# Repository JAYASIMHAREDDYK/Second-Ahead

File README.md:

# SECONDS AHEAD (A-ADAS)

<div align="center">

### Automotive Pre-Crash Early Warning, Dual-Sector Acoustic Radar & Kinematic Telemetry Cockpit

<!-- Primary System Badges -->
[-E63946?style=flat-square&logo=espressif&logoColor=white)](https://www.espressif.com/)
[-00B4D8?style=flat-square&logo=googlechrome&logoColor=white)](https://developer.mozilla.org/en-US/docs/Web/API/Web_Serial_API)

<br/>

<!-- Horizontal Mini Tech Stack Icons -->

<br/>

<!-- Performance Badges -->

</div>

<br/>

```
     [Front HC-SR04: Sensor A] ──┐
                                 ├──► [ESP32-H2 RISC-V SoC] ──► USB CDC UART (115200 8N1) ──► [Web Dashboard]
     [Side HC-SR04: Sensor B]  ──┤          ▲                                                        │
                                 │          │ 12ms Non-Blocking Acoustic Interleaving                ├─► Telemetry Cluster
     [TCRT5000 IR Contact: U4] ──┘          ▼                                                        ├─► 2D Kinematic Simulator
                                      [16x2 I2C LCD]                                                 └─► Trilingual Voice AI
```

---

## Table of Contents

- [Overview](#overview)
- [System Architecture](#system-architecture)
- [Key Technical Specifications](#key-technical-specifications)
- [Hardware Bench Wiring and Pinout Schedule](#hardware-bench-wiring-and-pinout-schedule)
- [Kinematics and Threat Assessment Engine](#kinematics-and-threat-assessment-engine)
- [High-Speed Telemetry Protocol](#high-speed-telemetry-protocol)
- [Telemetry Dashboard and 2D Incident Simulator](#telemetry-dashboard-and-2d-incident-simulator)
- [Trilingual Cockpit Voice AI](#trilingual-cockpit-voice-ai)
- [Ground-Truth Physical Impact Audit](#ground-truth-physical-impact-audit)
- [Getting Started](#getting-started)
- [Technical Dossier and Engineering Deliverables](#technical-dossier-and-engineering-deliverables)
- [Project Structure](#project-structure)
- [License](#license)

---

## Overview

**SECONDS AHEAD** is an automotive pre-crash detection and active cockpit alert system engineered on the **ESP32-H2 RISC-V microcontroller**. It bridges low-level real-time acoustic sensing with an instrument-grade web telemetry cluster and neural voice synthesis to deliver verifiable collision lead time.

Standard ultrasonic parking systems suffer from severe cross-echo interference, high cycle latency, and tunnel-vision frontal coverage that leaves intersection blind spots vulnerable. SECONDS AHEAD resolves these challenges through:

1. **Dual-Sector Acoustic Radar**: Frontal longitudinal tracking (**Sensor A**, 2–100 cm) paired with an orthogonal 90° lateral sensor (**Sensor B** for intersection cross-traffic), paced with 12ms non-blocking ping interleaving to prevent ultrasonic packet collisions.
2. **Deterministic Ground-Truth Lead-Time Audit**: An integrated **TCRT5000 infrared reflective sensor (U4)** positioned at the bumper barrier records the exact microsecond timestamp of physical impact. The system automatically computes and audits the advance warning margin ($\Delta t_{\text{lead}} = t_{\text{contact}} - t_{\text{warning}}$).
3. **Web Serial Telemetry Dashboard**: A zero-dependency single-file frontend running directly in Chromium-based browsers, visualizing live 20 Hz telemetry with rolling strip charts, dynamic proximity bars, and threat transition timelines.
4. **2D Kinematic Incident Simulator**: A real-time physics replayer simulating road kinematics, dual radar beam cones, lateral vehicle intrusions, safety boundaries, and collision shockwave dynamics.
5. **Trilingual Cockpit Voice AI**: Calm, authoritative ADAS audio warnings in **English**, **हिंदी (Hindi)**, and **ಕನ್ನಡ (Kannada)** powered by **ElevenLabs Creator Plan (Turbo v2.5)** with an in-memory audio object cache for **0 ms repeat latency**.

---

## System Architecture

```mermaid
graph TD
    subgraph Hardware ["Hardware Subsystem (ESP32-H2 Dev Module)"]
        SA["Sensor A: Front HC-SR04 (GPIO 10 / 11)"] -->|Longitudinal Ping| MCU["ESP32-H2 RISC-V SoC"]
        SB["Sensor B: Lateral HC-SR04 (GPIO 14 / 01)"] -->|12ms Interleaved Ping| MCU
        IR["Sensor U4: TCRT5000 IR (GPIO 12)"] -->|Bumper Impact Trigger| MCU
        BTN["Mute Switch (GPIO 24)"] -->|Mute Toggle| MCU

        MCU -->|I2C Fast Mode 400kHz| LCD["16x2 Character LCD (0x27)"]
        MCU -->|Parallel Digital Drive| LED_R["Red Strobe LEDs (High Risk)"]
        MCU -->|Digital Output| LED_B["Blue Monitor LED"]
        MCU -->|Tone Frequency Output| BZ["Acoustic Piezo Buzzer"]
    end

    subgraph Telemetry ["Serial Data Stream"]
        MCU -->|USB CDC UART 115200 8N1| WS["Web Serial Interface"]
    end

    subgraph Frontend ["Dashboard and Incident Simulator (index.html)"]
        WS --> PARSER["CSV Packet Parser"]
        PARSER --> CLUSTER["Telemetry Cluster (Gauges, Strip Chart, Timeline)"]
        PARSER --> SIM["2D Kinematic Simulator (Radar Cones, Car Physics)"]
        PARSER --> AUDIT["Ground-Truth Audit (Lead Time and Median Stats)"]
        PARSER --> VOICE["Neural Voice Engine (ElevenLabs Turbo / Web Speech)"]

        VOICE -->|Audio Playback| SPK["Trilingual Cockpit Audio"]
        SIM -->|MediaRecorder| VID["WebM Video Clip Exporter"]
        CLUSTER -->|Data Export| CSV["CSV Telemetry Downloader"]
    end
```

---

## Key Technical Specifications

| Parameter | Specification | Functional Details |
| :--- | :--- | :--- |
| **Microcontroller Unit** | ESP32-H2-DevKitM-1 | 32-bit RISC-V Single-Core @ 96 MHz, Native USB CDC |
| **Operating Voltage** | 3.3V DC Logic | Onboard LDO regulator with low-impedance common ground plane |
| **Longitudinal Sensor (A)** | HC-SR04 Ultrasonic | 2 cm to 100 cm active detection range, forward cone |
| **Lateral Sensor (B)** | HC-SR04 Ultrasonic | 90° blind-spot cross-traffic monitoring |
| **Interleaving Interval** | 12 ms non-blocking delay | Eliminates cross-reflection acoustic interference between sensors |
| **Ground-Truth Detector** | TCRT5000 Optical IR | Active-low bumper impact trigger for microsecond timestamping |
| **Telemetry Interface** | USB CDC Serial (115200 baud, 8N1) | Fixed-format ASCII CSV packets streamed at 18–20 Hz |
| **Cockpit Display** | 16x2 Character LCD | PCF8574 I2C backpack @ `0x27`, 400 kHz with 30ms timeout |
| **Visual Alert Indicators** | High-Intensity 5mm LEDs | Dual Red strobes (GPIO 0, 13) + Blue monitor LED (GPIO 4) |
| **Acoustic Sounder** | 3.3V Piezo Transducer | Pulsed frequency audio alert on GPIO 5 |
| **Dashboard Architecture** | Vanilla HTML5 / CSS3 / ES6 | Single zero-dependency file (`index.html`) using Web Serial API |
| **Voice AI Synthesis** | ElevenLabs `eleven_turbo_v2_5` | Sub-300ms neural streaming synthesis with 0ms memory cache |
| **Cockpit Alert Languages** | Trilingual (EN, HI, KN) | Authoritative, non-ragebaiting ADAS driving alerts |

---

## Hardware Bench Wiring and Pinout Schedule

<div align="center">
  
  <p><em>Figure 1: SECONDS AHEAD Hardware Prototype with numbered subsystem callouts.</em></p>
</div>

### Pinout Connection Schedule

| Pin Identifier | Signal Name | Connected Peripheral | Logic Level | Direction | Operational Role |
| :---: | :---: | :---: | :---: | :---: | :--- |
| **GPIO 10** | `TRIG_A` | Front HC-SR04 (Pin 2) | 3.3V | Output | 10 µs ultrasonic burst trigger |
| **GPIO 11** | `ECHO_A` | Front HC-SR04 (Pin 3) | 3.3V | Input | Longitudinal flight pulse measurement |
| **GPIO 14** | `TRIG_B` | Lateral HC-SR04 (Pin 2) | 3.3V | Output | 12 ms interleaved lateral burst trigger |
| **GPIO 01** | `ECHO_B` | Lateral HC-SR04 (Pin 3) | 3.3V | Input | Lateral acoustic flight measurement |
| **GPIO 12** | `PIN_IR` | TCRT5000 IR Sensor (OUT) | 3.3V | Input (PU) | Active LOW physical contact detection |
| **GPIO 22** | `I2C_SDA` | LCD PCF8574 Backpack | 3.3V | Bidirectional | I2C Serial Data (400 kHz Fast Mode) |
| **GPIO 23** | `I2C_SCL` | LCD PCF8574 Backpack | 3.3V | Output | I2C Serial Clock (30 ms timeout recovery) |
| **GPIO 00 & 13** | `RED_ALERT` | Red 5mm LEDs (Dual 220Ω) | 3.3V | Output | High-current parallel drive for HIGH_RISK strobe |
| **GPIO 04** | `BLUE_MON` | Blue 5mm LED (220Ω) | 3.3V | Output | Steady illumination for MONITOR threat level |
| **GPIO 05** | `BUZZER` | Piezo Buzzer Transducer | 3.3V | Output | Pulsed audible collision alarm |
| **GPIO 24** | `MUTE_SW` | Tactile Button to GND | 3.3V | Input (PU) | Active-low cockpit buzzer mute toggle |
| **3V3 & GND** | `PWR / GND`| Power Distribution Rails | 3.3V / 0V | Power | Regulated 3.3V power and ground return |

---

## Kinematics and Threat Assessment Engine

The ESP32-H2 firmware continuously calculates relative target kinematics using rolling median filtering and first-derivative linear regression.

### Mathematical Formulation

1. **Longitudinal Distance Measurement**:
   $$d(t) = \frac{\Delta t_{\text{echo}} \times 0.0343}{2} \quad [\text{cm}]$$

2. **Closing Velocity Calculation**:
   $$v(t) = -\frac{d(t) - d(t - \Delta t)}{\Delta t} \quad [\text{cm/s}]$$
   *(A positive velocity value denotes an object actively closing distance towards the vehicle).*

3. **Time-to-Collision (TTC)**:
   $$\text{TTC}(t) = \frac{d(t)}{v(t)} \quad [\text{s}]$$
   *(Computed only when $v(t) \ge 4.0\text{ cm/s}$. Evaluated as invalid ($-1.0\text{ s}$) when the target is static or receding).*

### Finite State Machine (FSM)

```
                            Target Observed (d <= 100 cm)
         ┌──────────────────────────────────────────────────────────────────┐
         │                                                                  │
         ▼                                                                  │
    ┌─────────┐         v < 4 cm/s          ┌──────────────┐                │
    │  WAIT   │ ──────────────────────────► │ NO APPROACH  │                │
    └─────────┘                             └──────────────┘                │
         ▲                                         │                        │
         │ No Target                               │ v >= 4 cm/s            │
         │                                         ▼                        │
         │                                  ┌──────────────┐                │
         │                                  │  UNCERTAIN   │ (Fast path)    │
         │                                  └──────────────┘                │
         │                                         │                        │
         │                                         │ Streak >= 2 & TTC > 3s │
         │                                         ▼                        │
         │                                  ┌──────────────┐                │
         │                                  │   MONITOR    │ (TTC 3.0s–5.0s)│
         │                                  └──────────────┘                │
         │                                         │                        │
         │                                         │ d < 50cm OR TTC <= 3.0s│
         │                                         ▼                        │
         │                                  ┌──────────────┐                │
         └───────────────────────────────── │  HIGH RISK   │ (Strobe/Alarm) │
              Physical Impact / Reset       └──────────────┘                │
                                                   │                        │
                                                   └────────────────────────┘
```

- **WAIT**: Target beyond 100 cm. All visual and audible alarms remain silent.
- **NO APPROACH**: Target detected within 100 cm but stationary or moving away ($v < 4\text{ cm/s}$).
- **UNCERTAIN**: Closing motion detected ($v \ge 4\text{ cm/s}$); establishing trajectory persistence over multiple pings.
- **MONITOR**: Verified approach trajectory with $3.0\text{ s} < \text{TTC} \le 5.0\text{ s}$ and $d > 50\text{ cm}$. Solid Blue LED enabled.
- **HIGH RISK**: Critical condition where $\text{TTC} \le 3.0\text{ s}$ or $d < 50\text{ cm}$. Triggers 3 Hz Red strobe LEDs, pulsed audio tone, and cockpit voice alert.

---

## High-Speed Telemetry Protocol

Telemetry is transmitted over USB CDC serial at **115200 baud, 8N1** in fixed-width comma-separated ASCII records at 18–20 Hz.

### Telemetry Packet Format
```
ms,dist_cm,speed_cms,ttc_s,state,ir,muted,side_cm
14250,38.2,21.4,1.78,HIGH RISK,1,0,68.4
```

| Field Index | Key | Units | Data Type | Definition |
| :---: | :--- | :---: | :---: | :--- |
| `0` | `ms` | milliseconds | integer | System elapsed uptime via `millis()` |
| `1` | `dist_cm` | centimeters | float | Sensor A longitudinal target distance |
| `2` | `speed_cms` | cm / second | float | Target closing speed relative to host |
| `3` | `ttc_s` | seconds | float | Time to collision; `-1.0` if inactive |
| `4` | `state` | — | string | Threat level: `WAIT`, `MONITOR`, `HIGH RISK` |
| `5` | `ir` | 0 or 1 | integer | TCRT5000 bumper state: `1` = CLEAR, `0` = CONTACT |
| `6` | `muted` | 0 or 1 | integer | Cockpit sounder state: `1` = MUTED, `0` = ARMED |
| `7` | `side_cm` | centimeters | float | Sensor B lateral blind-spot distance |

### Asynchronous Event Packet
```
IR_HIT,lead_ms=3450
```
Emitted via hardware interrupt the exact millisecond the TCRT5000 optical sensor detects bumper contact, delivering an independently verifiable audit of advance warning time.

---

## Telemetry Dashboard and 2D Incident Simulator

The frontend (`index.html`) is engineered with zero external libraries or bundle dependencies. It communicates directly with the hardware through the browser's native **Web Serial API**.

<div align="center">
  
  <p><em>Figure 2: Complete Electrical Interconnect and Signal Routing Schematic.</em></p>
</div>

### Operational View Modes

1. **Dashboard View (`[DASHBOARD]`)**:
   - Four primary instrument cards: **Distance**, **Speed**, **TTC**, and **Threat State**.
   - Dual-Sector readouts for Front Sensor A and Lateral Sensor B.
   - 30-second rolling strip chart with dynamic auto-scaling and threat zone fills.
   - High-contrast horizontal range bar with color-coded critical thresholds (50 cm danger marker).
   - 60-second historical threat timeline.
   - Ground-truth IR lead-time audit log with run statistics.

2. **Incident Simulator View (`[INCIDENT SIMULATOR]`)**:
   - 2D canvas simulation displaying highway lanes, ego vehicle, oncoming traffic, and lateral blind-spot cross-traffic.
   - Dynamic radar beam projection cones with live range expansion.
   - 50 cm perimeter boundary ring.
   - Animated shockwave burst on physical bumper contact.

3. **Split View (`[SPLIT VIEW]`)**:
   - Synchronized side-by-side display linking live telemetry readouts on the left with 2D kinematic canvas rendering on the right.

### Operator Features
- **Baud Rate Selector**: Configurable connection speeds (9600 to 921600 baud; default `115200`).
- **Interactive Console**: Slide-over raw serial terminal for inspecting streaming CSV strings and sending diagnostic commands.
- **Scenario Replayer**: Built-in test profiles (*Head-On Approach*, *Lateral Intrusion*, *Multi-Threat Scenario*) with variable playback rate (`0.5X`, `1X`, `2X`).
- **Video Clip Exporter (`RECORD CLIP`)**: Captures 30 FPS canvas streams directly to `.webm` video files.
- **Data Export (`EXPORT CSV`)**: Exports all captured session data with timestamps.

---

## Trilingual Cockpit Voice AI

The audio subsystem integrates the **ElevenLabs Creator Plan (`eleven_turbo_v2_5`)** to deliver calm, automotive-grade ADAS warning alerts. Phrasing is deliberately engineered to remain composed and authoritative, avoiding distracting repetitions or panic-inducing prompts.

<div align="center">

| Trigger Condition | English Prompt | हिंदी (Hindi) Prompt | ಕನ್ನಡ (Kannada) Prompt |
| :--- | :--- | :--- | :--- |
| **System Armed** | *"Collision warning system active."* | *"टक्कर चेतावनी प्रणाली सक्रिय है।"* | *"ಡಿಕ್ಕಿ ಎಚ್ಚರಿಕೆ ವ್ಯವಸ್ಥೆ ಸಕ್ರಿಯವಾಗಿದೆ."* |
| **High Collision Risk** | *"Caution. Collision risk ahead. Please brake."* | *"सावधान। आगे टक्कर का ख़तरा है। कृपया ब्रेक लगाएं।"* | *"ಎಚ್ಚರಿಕೆ. ಮುಂದೆ ಡಿಕ್ಕಿಯಾಗುವ ಸಾಧ್ಯತೆಯಿದೆ. ದಯವಿಟ್ಟು ಬ್ರೇಕ್ ಹಾಕಿ."* |
| **Oncoming Vehicle** | *"Vehicle approaching ahead."* | *"आगे से वाहन आ रहा है।"* | *"ಮುಂದೆ ವಾಹನ ಸಮೀಪಿಸುತ್ತಿದೆ."* |
| **Lateral Blind Spot** | *"Caution. Vehicle in side blind spot."* | *"सावधान। बगल में वाहन आ रहा है।"* | *"ಎಚ್ಚರಿಕೆ. ಪಕ್ಕದ ಬ್ಲೈಂಡ್ ಸ್ಪಾಟ್‌ನಲ್ಲಿ ವಾಹನವಿದೆ."* |

</div>

- **Language Selection**: Seamlessly switch between English, Hindi, and Kannada via the top-bar dropdown.
- **Zero-Latency In-Memory Caching**: Audio blobs are synthesized on initial trigger and cached as reusable browser audio objects, providing **0 ms latency** and zero additional API credit usage on subsequent triggers.
- **Offline Fallback**: If internet connectivity is interrupted, the system automatically falls back to native browser speech synthesis (`SpeechSynthesisUtterance`).

---

## Ground-Truth Physical Impact Audit

To provide definitive mathematical proof of safety efficacy for automotive judges and evaluators, SECONDS AHEAD implements a hardware-based ground-truth audit:

$$\text{Warning Lead Time } (\Delta t_{\text{lead}}) = t_{\text{contact}} - t_{\text{warning}}$$

```
Time Axis (ms) ──────────────────────────────────────────────────────────►
0 ms                  12,100 ms                           15,550 ms
│                     │                                   │
▼                     ▼                                   ▼
Approach Begins       HIGH RISK State Triggered           TCRT5000 Physical Impact
                      [Voice Alert + Strobes Fire]        [IR_HIT Event Logged]
                      └───────────────── 3,450 ms ───────┘
                                     Advance Warning Margin
```

Every run is indexed in the dashboard audit log, recording run count, target speed at initial warning, distance at warning, and verified lead time in milliseconds.

---

## Getting Started

### 1. Flash Firmware to ESP32-H2
1. Open `firmware/firmware.ino` in the Arduino IDE.
2. Select **Board**: `ESP32H2 Dev Module`.
3. Configure **USB CDC On Boot**: `Enabled`.
4. Install the required dependency `LiquidCrystal_I2C` via the Library Manager.
5. Connect your ESP32-H2 via USB-C and click **Upload**.

### 2. Launch the Web Dashboard
1. Open `index.html` in a Web Serial-compatible browser (Google Chrome, Microsoft Edge, or Opera).
2. Click **`CONNECT`** in the top control bar.
3. Select the ESP32-H2 USB serial device from the browser permission prompt.
4. Telemetry will begin streaming immediately at ~20 Hz.

### 3. Run Standalone Demonstration (No Hardware Required)
1. Open `index.html` in your browser.
2. Click **`DEMO`** in the top bar to generate synthetic dual-radar telemetry.
3. Select **`SPLIT VIEW`** or **`INCIDENT SIMULATOR`** to observe vehicle physics and radar cones reacting in real time.
4. Click **`▶ PLAY VIDEO`** to test simulated pre-crash scenarios.

---

## Technical Dossier and Engineering Deliverables

The repository includes a comprehensive five-part engineering submission dossier located in the `documentation/` directory:

1. **Schematic & Wiring Diagram**: [1_SCHEMATIC_AND_WIRING_DIAGRAM.pdf](documentation/1_SCHEMATIC_AND_WIRING_DIAGRAM.pdf)
2. **Annotated PCB Layout**: [2_PCB_LAYOUT_ANNOTATED.pdf](documentation/2_PCB_LAYOUT_ANNOTATED.pdf)
3. **Hardware Prototype Photography**: [3_BUILT_HARDWARE_ANNOTATED_PHOTOS.pdf](documentation/3_BUILT_HARDWARE_ANNOTATED_PHOTOS.pdf)
4. **Telemetry Dashboard & Simulator Overview**: [4_TELEMETRY_DASHBOARD_AND_SIMULATOR_SCREENS.pdf](documentation/4_TELEMETRY_DASHBOARD_AND_SIMULATOR_SCREENS.pdf)
5. **Bring-Up & Safety Validation Checklist**: [5_BRING_UP_AND_SAFETY_CHECKLIST.pdf](documentation/5_BRING_UP_AND_SAFETY_CHECKLIST.pdf)

---

## Project Structure

```
SECONDS-AHEAD/
├── firmware/
│   └── firmware.ino                    # ESP32-H2 C++ Arduino Firmware
├── index.html                          # Telemetry Dashboard, Simulator & Voice AI
├── annotated_hardware_top.jpg          # Hardware Prototype Photograph with Callouts
├── build_submission_dossier.py         # Automated ReportLab PDF Dossier Generator
├── documentation/
│   ├── 1_SCHEMATIC_AND_WIRING_DIAGRAM.pdf
│   ├── 2_PCB_LAYOUT_ANNOTATED.pdf
│   ├── 3_BUILT_HARDWARE_ANNOTATED_PHOTOS.pdf
│   ├── 4_TELEMETRY_DASHBOARD_AND_SIMULATOR_SCREENS.pdf
│   ├── 5_BRING_UP_AND_SAFETY_CHECKLIST.pdf
│   ├── kicad_schematic_clean.png
│   └── vector_wiring_diagram.png
├── kicad/
│   ├── seconds_ahead.kicad_pro         # KiCad 8.0 Project File
│   ├── seconds_ahead.kicad_pcb         # 2-Layer PCB Layout
│   └── seconds_ahead-rev-33.deeppcb    # Auto-routed PCB Artifact
└── README.md                           # Technical Documentation
```

---

## License

This project is released under the **MIT License**. You are free to inspect, modify, and deploy this architecture for academic, automotive safety, and embedded research applications.

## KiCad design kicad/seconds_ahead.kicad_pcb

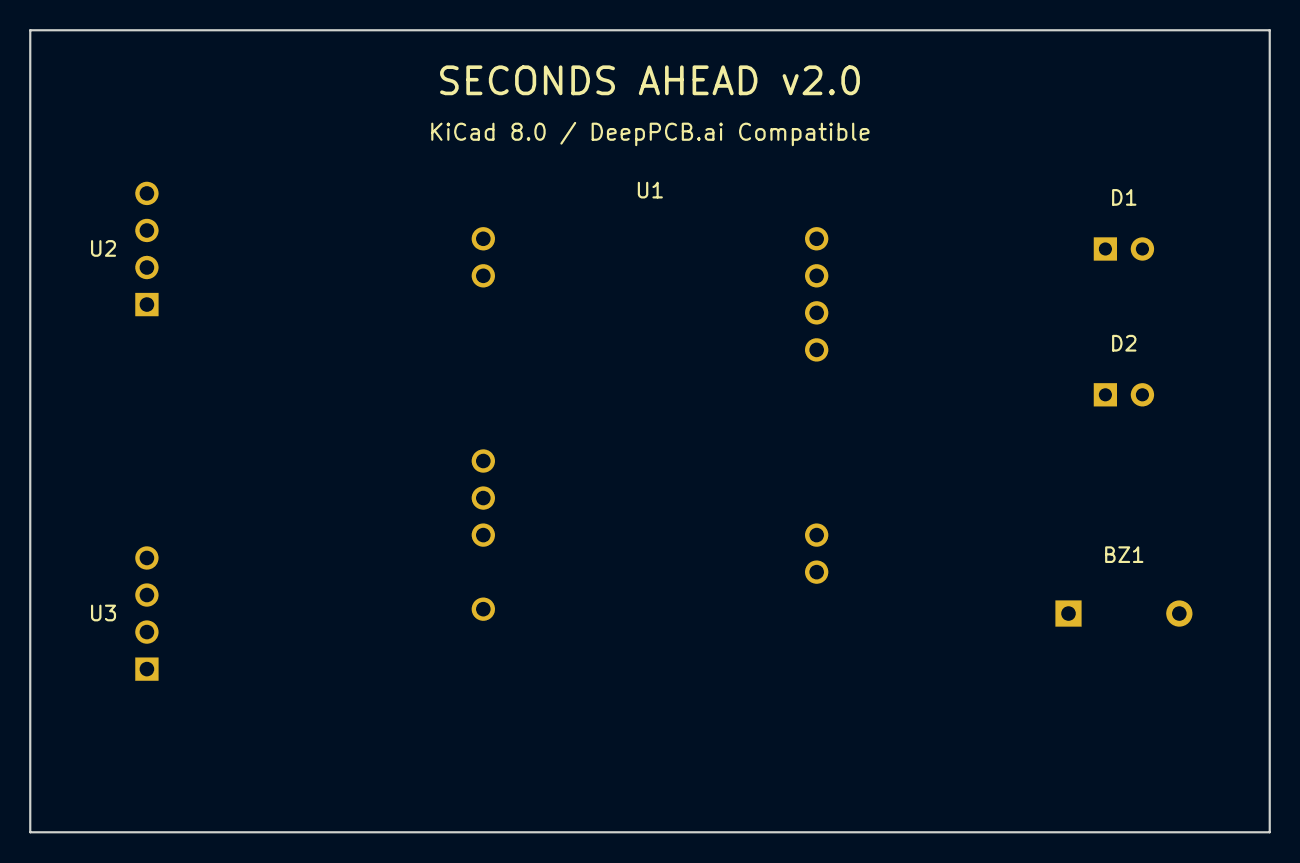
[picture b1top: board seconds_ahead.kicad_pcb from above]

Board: 2 copper layers, 85.0 x 55.0 mm, 6 parts (0 on the bottom side), 8 nets, no tracks yet.

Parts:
BZ1: BUZZER; Buzzer_12x9.5RM7.6
D1: RED_ALERT; LED_D5.0mm
D2: BLUE_MONITOR; LED_D5.0mm
U1: ESP32-H2; ESP32-H2-DevKitM-1
U2: HC-SR04_FRONT; PinHeader_1x04_P2.54mm_Vertical
U3: HC-SR04_LATERAL; PinHeader_1x04_P2.54mm_Vertical

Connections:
+3V3: U1.1, U2.1, U3.1
BLUE_MONITOR: D2.1, U1.4
BUZZER_ACT: BZ1.1, U1.5
ECHO_A: U1.11, U2.3
GND: BZ1.2, D1.2, D2.2, U1.2, U2.4, U3.4
RED_ALERT: D1.1, U1.0, U1.13
TRIG_A: U1.10, U2.2
TRIG_B: U1.14, U3.2

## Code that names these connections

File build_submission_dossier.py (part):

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        w_draw.text((x + w - 70, py), p_type, fill=(100, 116, 139))

draw_block(420, 70, 360, 410, "U1: ESP32-H2 (Glyph H2) Dev Module", [
    ("GPIO 10 [TRIG_A]", "3.3V OUT"),
    ("GPIO 11 [ECHO_A]", "3.3V IN"),
    ("GPIO 14 [TRIG_B]", "3.3V OUT"),
    ("GPIO 01 [ECHO_B]", "3.3V IN"),
    ("GPIO 12 [IR_SENSE]", "3.3V IN (PU)"),
    ("GPIO 24 [MUTE_BTN]", "3.3V IN (PU)"),
    ("GPIO 00 [RED_ALERT_0]", "3.3V OUT"),
    ("GPIO 13 [RED_ALERT_13]", "3.3V OUT"),
    ("GPIO 04 [BLUE_MONITOR]", "3.3V OUT"),
    ("GPIO 05 [PIN_BUZZER]", "3.3V OUT"),
    ("GPIO 22 [I2C_SDA]", "3.3V BI"),
    ("GPIO 23 [I2C_SCL]", "3.3V OUT"),
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sch_draw.text((470, 70), "U1: ESP32-H2-DevKitM-1 (96MHz)", fill=(255, 255, 255))

left_pins = [
    ("3V3 (1)", 120), ("GND (2)", 155), ("GPIO 10 [TRIG_A]", 200), ("GPIO 11 [ECHO_A]", 240),
    ("GPIO 14 [TRIG_B]", 290), ("GPIO 01 [ECHO_B]", 330), ("GPIO 12 [IR_SENSE]", 380), ("GPIO 24 [MUTE_BTN]", 430)
]
for p_name, py in left_pins:
    sch_draw.text((460, py - 6), p_name, fill=(15, 23, 42))
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
net_data = [
    [Paragraph("<b>Signal / Net Name</b>", body_style), Paragraph("<b>GPIO Pin</b>", body_style), Paragraph("<b>Connected Component &amp; Pin</b>", body_style), Paragraph("<b>Voltage Level</b>", body_style), Paragraph("<b>Electrical Function / Mode</b>", body_style)],
    [Paragraph("TRIG_A", mono_bold), Paragraph("GPIO 10", mono_style), Paragraph("U2 (Front HC-SR04), Pin 2 [TRIG]", body_style), Paragraph("3.3 V Logic", mono_style), Paragraph("10 µs acoustic transmit trigger pulse (OUTPUT)", body_style)],
    [Paragraph("ECHO_A", mono_bold), Paragraph("GPIO 11", mono_style), Paragraph("U2 (Front HC-SR04), Pin 3 [ECHO]", body_style), Paragraph("3.3 V Logic*", mono_style), Paragraph("Acoustic flight return pulse width (INPUT, 25ms timeout)", body_style)],
    [Paragraph("TRIG_B", mono_bold), Paragraph("GPIO 14", mono_style), Paragraph("U3 (Lateral HC-SR04), Pin 2 [TRIG]", body_style), Paragraph("3.3 V Logic", mono_style), Paragraph("12ms interleaved lateral ping trigger (OUTPUT)", body_style)],
    [Paragraph("ECHO_B", mono_bold), Paragraph("GPIO 01", mono_style), Paragraph("U3 (Lateral HC-SR04), Pin 3 [ECHO]", body_style), Paragraph("3.3 V Logic*", mono_style), Paragraph("Lateral acoustic flight return pulse (INPUT)", body_style)],
    [Paragraph("IR_CONTACT", mono_bold), Paragraph("GPIO 12", mono_style), Paragraph("U4 (TCRT5000 IR Sensor), Pin OUT", body_style), Paragraph("3.3 V Logic", mono_style), Paragraph("Active LOW physical contact detector (INPUT_PULLUP)", body_style)],
    [Paragraph("MUTE_BTN", mono_bold), Paragraph("GPIO 24", mono_style), Paragraph("SW1 (Mute Push Button), Pin 1", body_style), Paragraph("3.3 V Logic", mono_style), Paragraph("Push-to-GND audio mute toggle (INPUT_PULLUP)", body_style)],
    [Paragraph("RED_ALERT_0", mono_bold), Paragraph("GPIO 00", mono_style), Paragraph("D1 (Red 5mm LED), Anode via R1", body_style), Paragraph("3.3 V Logic", mono_style), Paragraph("Primary driver for HIGH_RISK strobe (OUTPUT)", body_style)],
    [Paragraph("RED_ALERT_13", mono_bold), Paragraph("GPIO 13", mono_style), Paragraph("D1 (Red 5mm LED), Anode via R1", body_style), Paragraph("3.3 V Logic", mono_style), Paragraph("Redundant parallel drive for Red LED (OUTPUT)", body_style)],
    [Paragraph("BLUE_MONITOR", mono_bold), Paragraph("GPIO 04", mono_style), Paragraph("D2 (Blue 5mm LED), Anode via R2", body_style), Paragraph("3.3 V Logic", mono_style), Paragraph("Active HIGH indicator for MONITOR approach state (OUTPUT)", body_style)],
    [Paragraph("BUZZER_ACT", mono_bold), Paragraph("GPIO 05", mono_style), Paragraph("BZ1 (Active Buzzer), Positive Terminal", body_style), Paragraph("3.3 V Logic", mono_style), Paragraph("150ms periodic audio beep on HIGH_RISK (OUTPUT)", body_style)],
    [Paragraph("I2C_SDA", mono_bold), Paragraph("GPIO 22", mono_style), Paragraph("LCD1 (1602 I2C Backpack), Pin SDA", body_style), Paragraph("3.3 V Logic*", mono_style), Paragraph("I2C Serial Data Bus (400kHz Fast Mode / Standard)", body_style)],
    [Paragraph("I2C_SCL", mono_bold), Paragraph("GPIO 23", mono_style), Paragraph("LCD1 (1602 I2C Backpack), Pin SCL", body_style), Paragraph("3.3 V Logic*", mono_style), Paragraph("I2C Serial Clock Line (30ms hardware timeout configured)", body_style)],
    [Paragraph("+3V3", mono_bold), Paragraph("3V3 Pin", mono_style), Paragraph("ESP32-H2 VDD, Sensors, LEDs, LCD", body_style), Paragraph("3.3 V DC", mono_style), Paragraph("Main system regulated logic power rail (max 500mA)", body_style)],
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story1.append(Paragraph("Point-to-Point Hardware Wiring Schedule", h1_style))
wire_schedule = [
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    [Paragraph("ESP32-H2 Pin 10", mono_style), Paragraph("TRIG_A", mono_bold), Paragraph("Front HC-SR04 Pin 2", body_style), Paragraph("ESP32 -> Sensor", body_style), Paragraph("3.3 V Logic", mono_style), Paragraph("Yellow wire -> Row 10", body_style)],
    [Paragraph("ESP32-H2 Pin 11", mono_style), Paragraph("ECHO_A", mono_bold), Paragraph("Front HC-SR04 Pin 3", body_style), Paragraph("Sensor -> ESP32", body_style), Paragraph("3.3 V Logic*", mono_style), Paragraph("White wire -> Row 11", body_style)],
    [Paragraph("ESP32-H2 Pin 14", mono_style), Paragraph("TRIG_B", mono_bold), Paragraph("Lateral HC-SR04 Pin 2", body_style), Paragraph("ESP32 -> Sensor", body_style), Paragraph("3.3 V Logic", mono_style), Paragraph("Green wire -> Row 14", body_style)],
    [Paragraph("ESP32-H2 Pin 01", mono_style), Paragraph("ECHO_B", mono_bold), Paragraph("Lateral HC-SR04 Pin 3", body_style), Paragraph("Sensor -> ESP32", body_style), Paragraph("3.3 V Logic*", mono_style), Paragraph("Blue wire -> Row 1", body_style)],
    [Paragraph("ESP32-H2 Pin 12", mono_style), Paragraph("PIN_IR", mono_bold), Paragraph("TCRT5000 Pin OUT", body_style), Paragraph("Sensor -> ESP32", body_style), Paragraph("3.3 V Logic", mono_style), Paragraph("Brown wire -> Row 12 (PU)", body_style)],
    [Paragraph("ESP32-H2 Pin 0/13", mono_style), Paragraph("RED_ALERT", mono_bold), Paragraph("Red LED Anode via 220R", body_style), Paragraph("ESP32 -> LED", body_style), Paragraph("3.3 V Logic", mono_style), Paragraph("Row 9 jumper to c9-c13", body_style)],
    [Paragraph("ESP32-H2 Pin 04", mono_style), Paragraph("BLUE_MONITOR", mono_bold), Paragraph("Blue LED Anode via 220R", body_style), Paragraph("ESP32 -> LED", body_style), Paragraph("3.3 V Logic", mono_style), Paragraph("Row 17 jumper to LED", body_style)],
    [Paragraph("ESP32-H2 Pin 05", mono_style), Paragraph("PIN_BUZZER", mono_bold), Paragraph("Active Buzzer Positive", body_style), Paragraph("ESP32 -> Buzzer", body_style), Paragraph("3.3 V Logic", mono_style), Paragraph("Row 5 jumper to Buzzer", body_style)],
    [Paragraph("ESP32-H2 Pin 22", mono_style), Paragraph("I2C_SDA", mono_bold), Paragraph("LCD Backpack Pin SDA", body_style), Paragraph("Bidirectional", body_style), Paragraph("3.3 V Logic*", mono_style), Paragraph("Yellow wire -> I2C SDA", body_style)],
    [Paragraph("ESP32-H2 Pin 23", mono_style), Paragraph("I2C_SCL", mono_bold), Paragraph("LCD Backpack Pin SCL", body_style), Paragraph("ESP32 -> LCD", body_style), Paragraph("3.3 V Logic*", mono_style), Paragraph("Orange wire -> I2C SCL", body_style)],
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

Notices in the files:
README.md:
License: MIT
